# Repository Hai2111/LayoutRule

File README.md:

# LayoutRule — PCB Layout Knowledge Base

> Cơ sở tri thức phục vụ **KiCadAutoLayout / Codex / Claude**: placement, routing, PCB review, DRC, DFM.

**Đọc trước tiên:** [START_HERE.md](START_HERE.md) — 1 trang quy trình cho cả owner và agent. Đề bài board mới: [PROJECT_INTAKE.md](PROJECT_INTAKE.md) — 10 câu hỏi giao bài; thông tin thiếu được ghi thành giả định, không dừng flow.

**Cập nhật:** 2026-11-23 (đang đề xuất PR #5) · **Trạng thái:** core approved — quy tắc A/P/R/G (LAYOUT_RULES), playbook vòng lặp theo vùng (ITERATIVE_ROUTING_PLAYBOOK, H1/H2 + visual scan 3 tầng), rule 001 starter (tham số DRAFT, fab cross-checked, DRC chưa chạy) và topology digest format (class boundaries đã chốt). Phần catalog video/reference vẫn là research v0.3: metadata/chapters, chưa xác minh toàn văn.

## Quy trình cho agent tự làm layout (approved 2026-11-20, owner Hai)
- [ITERATIVE_ROUTING_PLAYBOOK.md](ITERATIVE_ROUTING_PLAYBOOK.md) — **cách làm chính hiện hành**: chia vùng R1→R4, vòng lặp *đặt → route (agent quyết định, tool thực thi) → ảnh 3 tầng → logic*, 3 bất biến INV-1/2/3, 2 hành vi chuẩn H1 (route ⇄ xê linh kiện xuyên suốt) + H2 (ảnh ratsnest là bản đồ đầu vào), báo cáo vùng = **1 ảnh + ≤5 dòng** cho owner.
- [AGENT_LAYOUT_PLAYBOOK.md](AGENT_LAYOUT_PLAYBOOK.md) — quy trình 5 pha có cổng kiểm (intent → floorplan → placement → routing → kiểm chức năng), giữ làm nền cho các cổng.
- [rules/layout_defaults.json](rules/layout_defaults.json) — giá trị khởi điểm (bề rộng theo dòng, số via đổi lớp, khoảng cách decoupling, vòng nóng…); mỗi giá trị ghi rõ `VENDOR` / `CALC` / `PRACTICE`.
- [rules/001-general-layout.md](rules/001-general-layout.md) — rule starter "general layout & clearance" cho board prototype FR-4 2–4 lớp; tham số DRAFT (đã cross-check fab, DRC validation PENDING).
- [rules/topology_digests.json](rules/topology_digests.json) — digest "input nhỏ" để 1 session đọc/hiểu ref design không cần parse cả file CAD; class boundaries light/medium/heavy đã chốt.
- [tools/layout_audit.py](tools/layout_audit.py) — đo hình học `.kicad_pcb` so với `layout_intent.json`; mới thử trên board tổng hợp trong `tests/fixtures/`, chưa thử trên board KiCad 10 thật.
- [FREEROUTING_VISUAL_LOOP.md](FREEROUTING_VISUAL_LOOP.md) — **Freerouting + ảnh PCB 2D + agent local** + `STAGE_REPORT.html`/`stage_results.json` minh bạch từng bước (ảnh gốc KiCad SVG→PNG, ROI, giả thuyết lỗi, KEEP/ROLLBACK có SHA): tự thử đổi placement/rip-up net, reroute, đo DRC và rollback. Thử nghiệm: chưa chạy end-to-end trên KiCad local.
- [CLOSED_LOOP_RUNBOOK.md](CLOSED_LOOP_RUNBOOK.md) — **vòng lặp local thật**: Codex/Claude quyết định → Python `pcbnew` sửa candidate → KiCad DRC + ảnh F.Cu/B.Cu → KEEP/ROLLBACK; chưa xác minh end-to-end bằng KiCad host.
- [tools/layout_controller.py](tools/layout_controller.py) — điều phối vòng lặp; `layout_observer.py`, `kicad_executor.py`, `candidate_evaluator.py` thực thi/kiểm chứng, không khóa board.
- [rules/owner_decisions.json](rules/owner_decisions.json) — **dữ liệu gốc Q01–Q35**: 32 lựa chọn A/B/C, Q22 xác nhận bằng lời, Q14/Q35 chưa chọn; các quyết định mới thay thế được đánh dấu rõ để agent không áp dụng rule cũ.
- [REVIEW_LEARNING_LOOP.md](REVIEW_LEARNING_LOOP.md) — **owner chỉ review bản cuối sau báo cáo**, agent giữ nguyên văn góp ý, đọc lại ở phiên sau; không khóa vùng/linh kiện trừ neo cơ khí và không tự công nhận rule.\n- [SESSION_PIPELINE.md](SESSION_PIPELINE.md) — **ONE SESSION = ONE OWNER REVIEW**: reference phải đủ bằng chứng trước routing, thiếu là GLOBAL STOP; hai candidate trên branch riêng; 1 ảnh tổng hợp và tối đa 5 dòng để chủ duyệt cuối phiên.

## Autolayout đã học (PROPOSED 2026-11-26)
- [AUTOLAYOUT_LEARNED.md](AUTOLAYOUT_LEARNED.md) — tổng hợp 20 bài học, quy trình tác tử quan sát (nhìn ảnh → sửa đúng chỗ → DRC), so sánh với Vector; mã trong [autolayout/](autolayout/).

## Routing engine (bổ sung 2026-11-15)
- [ROUTING_ENGINE_INTEGRATION.md](ROUTING_ENGINE_INTEGRATION.md) — so sánh Freerouting DSN/SES và PCBWorld/CADET, luật routing + cách kiểm tra native DRC. Code thử nghiệm đã commit trong [Hai2111/Training/routing](https://github.com/Hai2111/Training/tree/main/routing).
- [tools/route_pipeline.ps1](tools/route_pipeline.ps1) — cổng reference bắt buộc; nhận CandidateBoard do agent tạo hoặc FreeroutingProposal thử nghiệm; native KiCad DRC + geometry audit. Xem [setup/SMOKE_TEST.md](setup/SMOKE_TEST.md) cho giới hạn đã xác minh.

## Tư liệu tham khảo (CHỈ agent cần đào sâu đọc — không thuộc quy trình mặc định, xem START_HERE.md)
1. [VIDEO_CATALOG.md](VIDEO_CATALOG.md) — **43 video** Phil's Lab / Altium Academy.
2. [VIDEO_REVIEWS_EXTERNAL.md](VIDEO_REVIEWS_EXTERNAL.md) — **25 video review** ngoài hai kênh: Robert Feranec/FEDEVEL, EEVblog, element14.
3. [REFERENCE_DESIGN_CATALOG.md](REFERENCE_DESIGN_CATALOG.md) — **36 nguồn reference PCB/hãng**, mức xác minh khác nhau.
4. [PLACEMENT_PATTERNS.md](PLACEMENT_PATTERNS.md) — **16 pattern có điều kiện**, từ mechanical freeze tới source-specific crystal placement.
5. [LAYOUT_RULES.md](LAYOUT_RULES.md) — bộ quy tắc có ID, điều kiện áp dụng, ngoại lệ và cách kiểm tra.
6. [PLACEMENT_ROUTING_WORKFLOW.md](PLACEMENT_ROUTING_WORKFLOW.md) — thứ tự placement / routing dành cho agent.
7. [REVIEW_CHECKLIST.md](REVIEW_CHECKLIST.md) — tiêu chí PASS/FAIL và yêu cầu bằng chứng.
8. [AGENTS.md](AGENTS.md) — yêu cầu Codex/Claude kế thừa và kiểm chứng quy tắc.
9. [tools/catalog_status.py](tools/catalog_status.py) — tạo thống kê video CSV/JSON.
10. [rules/placement_patterns.json](rules/placement_patterns.json) — dữ liệu machine-readable **16 placement patterns**, chưa gắn engine kiểm tra tự động.
11. [references/index.json](references/index.json) — danh mục có cấu trúc cho **36 reference design**, xác minh theo cấp độ.
12. [tools/reference_status.py](tools/reference_status.py) — kiểm tra index/MD đồng nhất và xuất CSV.
13. [TECHNICAL_SOURCES.md](TECHNICAL_SOURCES.md) — 17 nguồn tiêu chuẩn/tài liệu hãng/KiCad (TS14–TS17 là đề xuất mới) có mức bằng chứng rõ ràng.
14. [rules/technical_checks.json](rules/technical_checks.json) — 10 đề xuất kiểm tra layout có inputs và điều kiện, **chưa thực thi**.
15. [references/RD30_kicad_placement_sample.json](references/RD30_kicad_placement_sample.json) — 1 bộ dữ liệu vị trí + net được trích trực tiếp từ KiCad source, có SHA.
16. [AI_LAYOUT_RESEARCH.md](AI_LAYOUT_RESEARCH.md) — 7 paper/repo khoa học, bao gồm CADET + PCBWorld và thiết kế benchmark KiCadAutoLayout.

## Nguyên tắc quan trọng
- **Không coi link / chapter / description là bằng chứng đã xem toàn bộ video.** Trạng thái mặc định là `SOURCE_METADATA_REVIEWED`; khi có transcript hoặc phân tích trực tiếp mới nâng cấp và ghi URL + timestamp/đoạn hỗ trợ.
- **Không dùng luật tuyệt đối thiếu cơ sở**, ví dụ “cấm góc 90° ở mọi trace”, “mọi tụ phải gần nhất về hình học”, hoặc “đi tất cả power trước mọi signal”.
- **Prioritize device-specific source:** Espressif ESP32-S3 crystal guide đề nghị gap >=2.0 mm tới clock pin; không suy ra đó là ngưỡng chung cho MCU khác. Xem RD03/PT04.
- **DRC=0 là điều kiện cần, không đủ**; agent còn phải kiểm tra topology, return path, vòng dòng chuyển mạch, nhiệt, khả năng sản xuất và rủi ro EMI/SI.
- Các giới hạn chiều rộng, clearance, via, impedance **lấy từ nhà sản xuất, stackup và từng dự án**, không khóa cứng thành một cấu hình cho mọi board.

**Tổng catalog video: 68 video = 37 Phil's Lab + 6 Altium Academy + 25 nguồn ngoài; trạng thái metadata/chapter M=68, transcript/video full T/V=0.** Không tuyên bố đã xem hết.

**Kiểm tra reference:** chạy `python tools/reference_status.py --csv-output report/references.csv` tại root repo. Hiện **1/36** reference đã được đọc một phần placement/net từ CAD (RD30), **0/36** đã parse/verify toàn bộ geometry + DRC/electrical performance; các luật hình học khác còn là candidates.

**Kiểm tra số video:** chạy `python tools/catalog_status.py --json-output report/videos.json --csv-output report/videos.csv` tại root repo. Không chứa transcript có bản quyền.

## Áp dụng vào KiCadAutoLayout
1. Đọc netlist/schematic, footprint, datasheet, stackup và PCB constraints.
2. Lập placement constraints, gán functional blocks và critical nets.
3. Placement theo các phase trong workflow; chạy kiểm tra sau từng phase.
4. Route theo độ ưu tiên kỹ thuật, không theo thứ tự tên net.
5. Chạy DRC/ERC, đối soát net connectivity + checklist độc lập, xuất báo cáo `rule_id | evidence | result | proposed_change`.
6. Mỗi lần người dùng sửa PCB: so sánh thay đổi và tránh ghi đè chỉnh sửa thủ công không có lý do kỹ thuật và bằng chứng.

## Quy định cập nhật
Mỗi video mới phải thêm một bản ghi trong `VIDEO_CATALOG.md` với: source, ngày, mức xác minh, mốc thời gian, tóm tắt, rule IDs, điểm cần xác minh tiếp. Rule mới chỉ được gắn `HARD` khi có điều kiện kỹ thuật/tiêu chuẩn hoặc thông số nhà sản xuất để kiểm tra.

**Nguồn chính:** [Phil's Lab](https://www.phils-lab.net/videos), [Altium Academy](https://www.youtube.com/@AltiumAcademy), tài liệu [Altium Component Placement & Routing](https://www.altium.com/documentation/altium-designer/tutorial/component-placement-routing-board). Nội dung trong repo là bản tóm tắt và đề xuất kiểm tra kỹ thuật, không sao chép transcript có bản quyền.

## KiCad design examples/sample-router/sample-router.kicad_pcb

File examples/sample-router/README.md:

# sample-router — dự án mẫu 1-lệnh cho agent

**Mục đích:** dự án nhỏ, **KiCad-native sạch** (không phải board convert Altium) để 1 session agent chạy được **cả chuỗi routing + kiểm tra** từ repo, làm bước kiểm thử cho pipeline. Board convert Altium (RA01) chưa export được DSN (xem `setup/SMOKE_TEST.md`) nên demo phải dùng board native.

## Nó có gì
- `sample-router.kicad_pcb` — 2 lớp, **6 component, 10 net, 14 segment + 3 via đã có sẵn**, GND plane lớp B.Cu, một phần routing (chưa hoàn chỉnh — có net chưa nối).
- `layout_intent.json` — intent mẫu (net class, decoupling, hot loop, diff pair USB) đúng schema `AGENT_LAYOUT_PLAYBOOK.md`.
- `sample-router.kicad_pro` — design rules min 0.2 mm, class mặc định.

## Agent chạy thế nào (theo đúng ITERATIVE_ROUTING_PLAYBOOK)
```powershell
# 0) toolchain
powershell -NoProfile -ExecutionPolicy Bypass -File setup\setup.ps1
# 1) routing candidate (1 lệnh, không ghi đè board gốc)
powershell -NoProfile -ExecutionPolicy Bypass -File tools\route_pipeline.ps1 -Board examples\sample-router\sample-router.kicad_pcb
```
Pipeline ra (trong `examples/sample-router/routing_candidate/`):
`sample-router.dsn` → Freerouting JAR → `sample-router.ses` → import vào **candidate riêng** `sample-router-routed.kicad_pcb` → DRC json → **ảnh 3D PNG**.

Sau đó agent làm đúng vòng lặp §3: visual pass 3 tầng + logic pass (INV-1/2/3) trên candidate, rồi báo cáo theo §3.5 = **1 ảnh + ≤5 dòng** cho owner. Board gốc `sample-router.kicad_pcb` không bao giờ bị ghi đè.

## Chờ mong đợi khi owner xem
- Ảnh 3D + 5 dòng vấn đề (đúng format §3.5).
- DRC candidate có thể còn vi phạm/via không nối — điều này **cố ý**: pipeline chỉ tạo *candidate*, agent phải iter (H1: xê linh kiện → route lại) rồi mới giao. Freerouting "0 unrouted" không đồng nghĩa đạt chuẩn (rule R13/G05).

## Kết quả hiện tại (baseline, 2026-11-23)
- Board nguồn `sample-router.kicad_pcb` ở trạng thái **0 unconnected** (đã dọn các tự-xung-đột cũ của fixture).
- Pipeline (MaxPasses 8) → candidate: **0 unconnected**, Freerouting score 1000 (0 unrouted / 0 router violation).
- Ảnh `routing_candidate/sample-router-routed.png` được pipeline **tự sinh lại** mỗi lần chạy (không vẽ tay).
- Vẫn còn (giữ làm **bài H1 cho agent**): ~3–4 góc vuông 90° ở cụm nguồn U2/L1/C1 (F.Cu) + ~4 trace 0.15 mm dưới min DRC 0.2 mm + 1 orphan via. **Cách xử lý đúng** = H1 trong playbook (xê linh kiện → route lại 45°), không phải chỉnh ảnh.
- Lưu ý: mỗi lần xê linh kiện có thể sinh lỗi mới (đã kiểm chứng xê C1 → GND U2 mất nối), nên giữ baseline 0-unconnected; agent phải cân bằng.

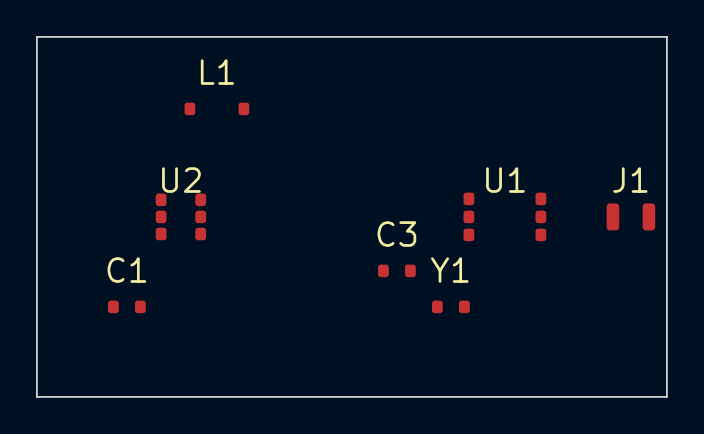
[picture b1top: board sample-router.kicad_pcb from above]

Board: 2 copper layers, 35.0 x 20.0 mm, 7 parts (0 on the bottom side), 8 nets, no tracks yet.

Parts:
C1: C1
C3: C3
J1: J1
L1: L1
U1: U1
U2: U2
Y1: Y1

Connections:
+3V3: C3.2, L1.1, U1.1, U2.1, U2.3
+5V: C1.2, U2.5
GND: C1.1, C3.1, U1.2, U2.4
SW: L1.2, U2.6
USB_DN: J1.2, U1.6
USB_DP: J1.1, U1.5
XI: U1.3, Y1.1
XO: U1.4, Y1.2
